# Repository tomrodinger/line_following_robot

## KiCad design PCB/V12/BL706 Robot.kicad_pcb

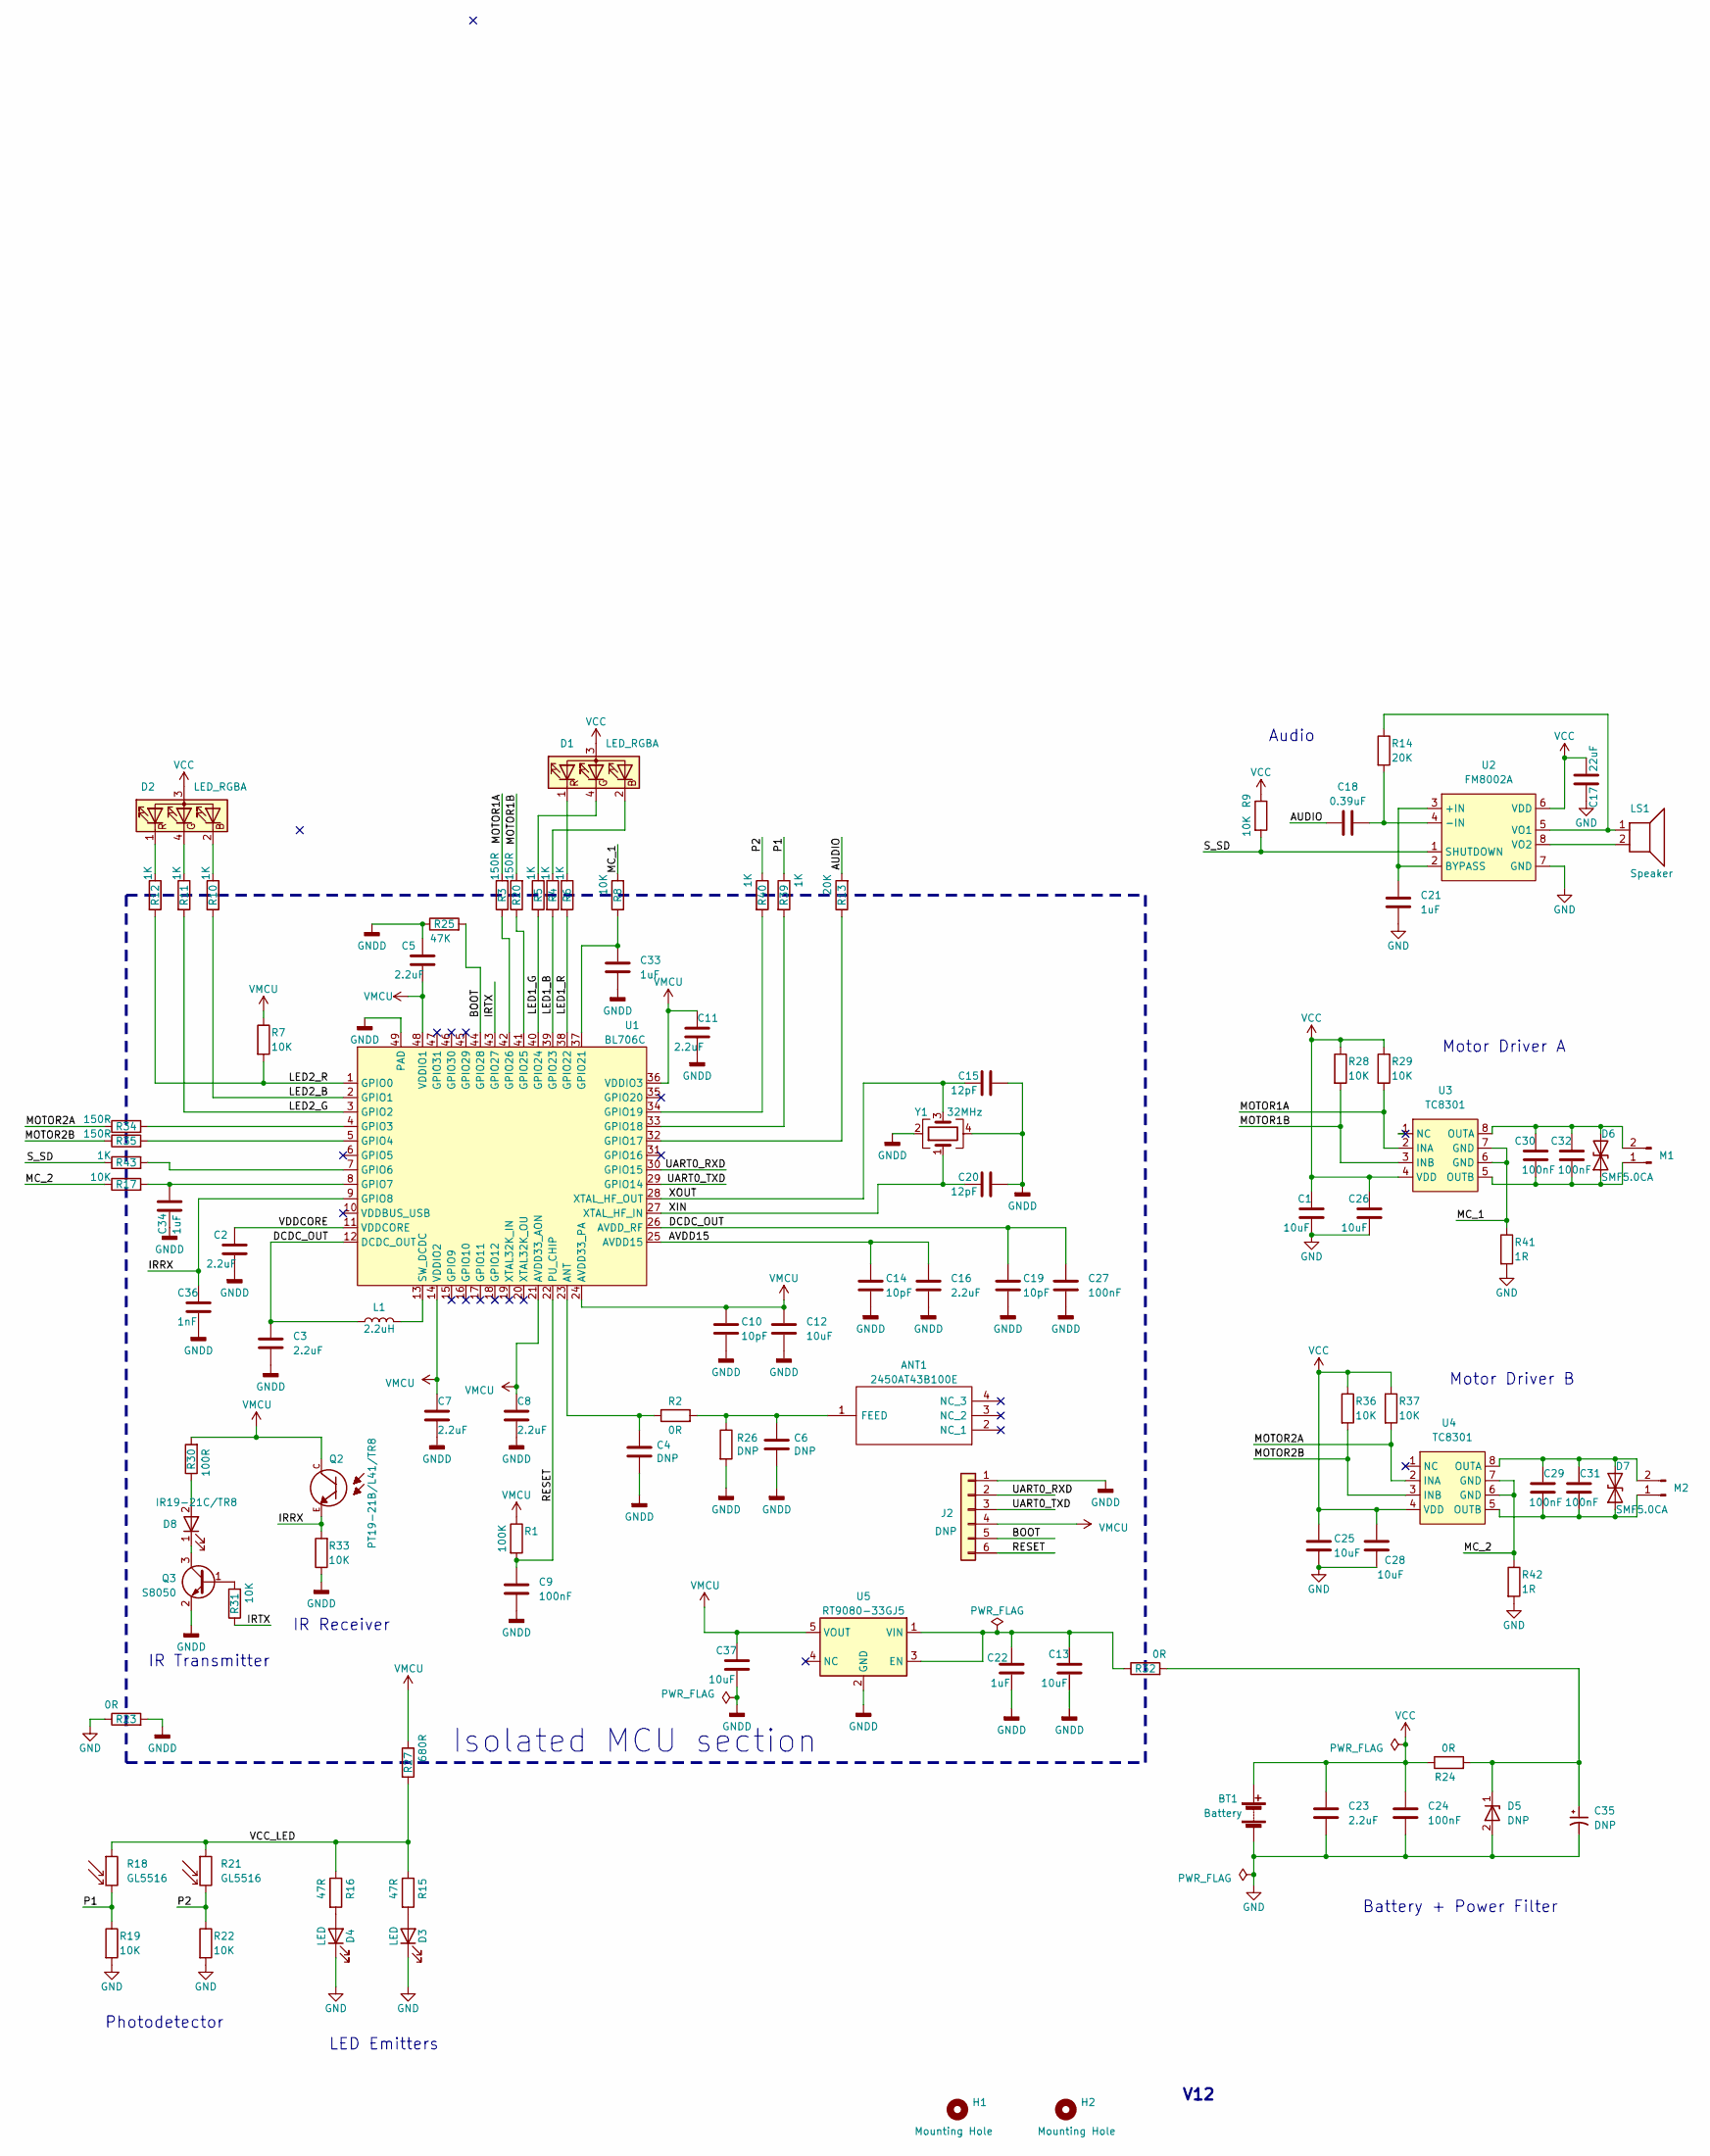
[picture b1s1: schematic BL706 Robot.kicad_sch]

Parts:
ANT1: 2450AT43B100E; LCSC C2917721
BT1: Battery; JST_PH_B2B-PH-K_1x02_P2.00mm_Vertical; LCSC C131337
C1, C12, C13, C25, C26, C28: 10uF; C_0603_1608Metric; LCSC C96446
C2, C3, C5, C7, C8, C11, C16, C23: 2.2uF; C_0402_1005Metric; LCSC C12530
C4, C6: DNP; C_0402_1005Metric
C9, C24, C27, C29, C30, C31, C32: 100nF; C_0402_1005Metric; LCSC C307331
C10, C14, C19: 10pF; C_0402_1005Metric; LCSC C32949
C15, C20: 12pF; C_0402_1005Metric; LCSC C1547
C17: 22uF; C_0603_1608Metric; LCSC C162690
C18: 0.39uF; C_0603_1608Metric; LCSC C309480
C21, C22: 1uF; C_0603_1608Metric; LCSC C15849
C33, C34: 1uF; C_0402_1005Metric; LCSC C52923
C35: DNP; CP_Elec_8x10.5; LCSC DNP
C36: 1nF; C_0402_1005Metric; LCSC C1523
C37: 10uF; C_1206_3216Metric; LCSC C13585
D1, D2: LED_RGBA; FM-B2020RGBA-HG; LCSC C108793
D3, D4: LED; LED_D3.0mm_Horizontal_O1.27mm_Z2.0mm
D5: DNP; D_MELF; LCSC DNP
D6, D7: SMF5.0CA; D_SOD-123F; LCSC C320548
D8: IR19-21C/TR8; IR19-21C-TR8; LCSC C142316
H1, H2: Mounting Hole; MountingHole_3mm
J2: DNP; PinHeader_1x06_P1.27mm_Vertical
L1: 2.2uH; L_0805_2012Metric; LCSC C86089
LS1: Speaker; JST_XH_B2B-XH-A_1x02_P2.50mm_Vertical; LCSC C158012
M1, M2: Conn_01x02_Male; JST_XH_B2B-XH-A_1x02_P2.50mm_Vertical; LCSC C158012
Q2: PT19-21B/L41/TR8; XDCR_PT19-21B_L41_TR8; LCSC C131258
Q3: S8050; SOT-23-3; LCSC C2926165
R1: 100K; R_0402_1005Metric; LCSC C25741
R2: 0R; R_0402_1005Metric; LCSC C17168
R3, R20, R34, R35: 150R; R_0402_1005Metric; LCSC C25082
R4, R5, R6, R10, R11, R12, R39, R40, R43: 1K; R_0402_1005Metric; LCSC C11702
R7, R8, R9, R17, R19, R22, R28, R29, R31, R33: 10K; R_0402_1005Metric; LCSC C25744
R13, R14: 20K; R_0402_1005Metric; LCSC C25765
R15, R16: 47R; R_0402_1005Metric; LCSC C25118
R18, R21: GL5516; R_LDR_5.0x4.1mm_P3mm_Vertical; LCSC C125626
R23, R24, R32: 0R; R_1206_3216Metric; LCSC C17888
R25: 47K; R_0402_1005Metric; LCSC C25792
R26: DNP; R_0402_1005Metric
R27: 680R; R_0805_2012Metric; LCSC C17798
R30: 100R; R_0402_1005Metric; LCSC C25076
R36, R37: 10K; R_0402_1005Metric; LCSC PN C25744
R41, R42: 1R; R_1206_3216Metric; LCSC C17928
U1: BL706C; QFN-48-1EP_6x6mm_P0.4mm_EP4.3x4.3mm; LCSC C2874060
U2: FM8002A; SOP-8_3.9x4.9mm_P1.27mm; LCSC C94625
U3, U4: TC8301; SOP-8_3.9x4.9mm_P1.27mm; LCSC C2887481
U5: RT9080-33GJ5; TSOT-23-5; LCSC C841192
Y1: 32MHz; Crystal_SMD_2016-4Pin_2.0x1.6mm; LCSC C255896

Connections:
/AUDIO: C18.1, R13.2
/AVDD15: C14.1, C16.1, U1.25 (AVDD15)
/BOOT: J2.5, R25.2, U1.44 (GPIO28)
/DCDC_OUT: C3.1, C19.1, C27.1, L1.1, U1.12 (DCDC_OUT), U1.26 (AVDD_RF)
/IRRX: C36.1, Q2.E, R33.2, U1.9 (GPIO8)
/IRTX: R31.1, U1.43 (GPIO27)
/LED1_B: R4.2, U1.39 (GPIO23)
/LED1_G: R5.2, U1.40 (GPIO24)
/LED1_R: R6.2, U1.38 (GPIO22)
/LED2_B: R10.2, U1.2 (GPIO1)
/LED2_G: R11.2, U1.3 (GPIO2)
/LED2_R: R7.2, R12.2, U1.1 (GPIO0)
/MC_1: R8.2, R41.1, U3.6 (GND), U3.7 (GND)
/MC_2: R17.1, R42.1, U4.6 (GND), U4.7 (GND)
/MOTOR1A: R3.2, R29.2, U3.2 (INA)
/MOTOR1B: R20.2, R28.2, U3.3 (INB)
/MOTOR2A: R34.1, R37.2, U4.2 (INA)
/MOTOR2B: R35.1, R36.2, U4.3 (INB)
/P1: R18.2, R19.1, R39.1
/P2: R21.2, R22.1, R40.1
/RESET: C9.1, J2.6, R1.2, U1.22 (PU_CHIP)
/S_SD: R9.2, R43.1, U2.1 (SHUTDOWN)
/UART0_RXD: J2.2, U1.30 (GPIO15)
/UART0_TXD: J2.3, U1.29 (GPIO14)
/VCC_LED: R15.1, R16.1, R18.1, R21.1, R27.2
/VDDCORE: C2.1, U1.11 (VDDCORE)
/XIN: C20.2, U1.27 (XTAL_HF_IN), Y1.1
/XOUT: C15.2, U1.28 (XTAL_HF_OUT), Y1.3
GND: BT1.2 (-), C1.2, C17.2, C21.2, C23.2, C24.2, C25.2, C26.2, C28.2, C35.2, D3.1 (K), D4.1 (K), D5.2 (A), R19.2, R22.2, R23.1, R41.2, R42.2, U2.7 (GND)
GNDD: C2.2, C3.2, C4.2, C5.1, C6.2, C7.2, C8.2, C9.2, C10.2, C11.1, C12.2, C13.2, C14.2, C15.1, C16.2, C19.2, C20.1, C22.2, C27.2, C33.2, C34.2, C36.2, C37.2, J2.1, Q3.2 (E), R23.2, R25.1, R26.2, R33.1, U1.49 (PAD), U5.2 (GND), Y1.2, Y1.4
unnamed: ANT1.1 (FEED), C6.1, R2.2, R26.1
unnamed: D1.2 (BK), R4.1
unnamed: D1.4 (GK), R5.1
unnamed: D1.1 (RK), R6.1
unnamed: D2.2 (BK), R10.1
unnamed: D2.4 (GK), R11.1
unnamed: D2.1 (RK), R12.1
unnamed: D3.2 (A), R15.2
unnamed: D4.2 (A), R16.2
unnamed: C35.1, D5.1 (K), R24.2, R32.2
unnamed: C30.2, C32.2, D6.1 (A1), M1.1, U3.5 (OUTB)
unnamed: C30.1, C32.1, D6.2 (A2), M1.2, U3.8 (OUTA)
unnamed: C29.2, C31.2, D7.1 (A1), M2.1, U4.5 (OUTB)
unnamed: C29.1, C31.1, D7.2 (A2), M2.2, U4.8 (OUTA)
unnamed: D8.2 (A), R30.1
unnamed: D8.1 (K), Q3.3 (C)
unnamed: Q3.1 (B), R31.2
unnamed: C4.1, R2.1, U1.23 (ANT)
unnamed: R34.2, U1.4 (GPIO3)
unnamed: R35.2, U1.5 (GPIO4)
unnamed: R43.2, U1.7 (GPIO6)
unnamed: C34.1, R17.2, U1.8 (GPIO7)
unnamed: R13.1, U1.32 (GPIO17)
unnamed: R39.2, U1.33 (GPIO18)
unnamed: R40.2, U1.34 (GPIO19)
unnamed: C33.1, R8.1, U1.37 (GPIO21)
unnamed: R20.1, U1.41 (GPIO25)
unnamed: R3.1, U1.42 (GPIO26)
unnamed: L1.2, U1.13 (SW_DCDC)
unnamed: C21.1, U2.2 (BYPASS), U2.3 (+IN)
unnamed: C18.2, R14.2, U2.4 (-IN)
unnamed: LS1.1, R14.1, U2.5 (VO1)
unnamed: LS1.2, U2.8 (VO2)
unnamed: C13.1, C22.1, R32.1, U5.1 (VIN), U5.3 (EN)
VCC: BT1.1 (+), C1.1, C17.1, C23.1, C24.1, C25.1, C26.1, C28.1, D1.3 (A), D2.3 (A), R9.1, R24.1, R28.1, R29.1, R36.1, R37.1, U2.6 (VDD), U3.4 (VDD), U4.4 (VDD)
VPP: C5.2, C7.1, C8.1, C10.1, C11.2, C12.1, C37.1, J2.4, Q2.C, R1.1, R7.1, R27.1, R30.2, U1.14 (VDDIO2), U1.21 (AVDD33_AON), U1.24 (AVDD33_PA), U1.36 (VDDIO3), U1.48 (VDDIO1), U5.5 (VOUT)

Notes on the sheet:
Photodetector
Audio
LED Emitters
Motor Driver A
Battery + Power Filter
Isolated MCU section
V12
IR Transmitter
Motor Driver B
IR Receiver

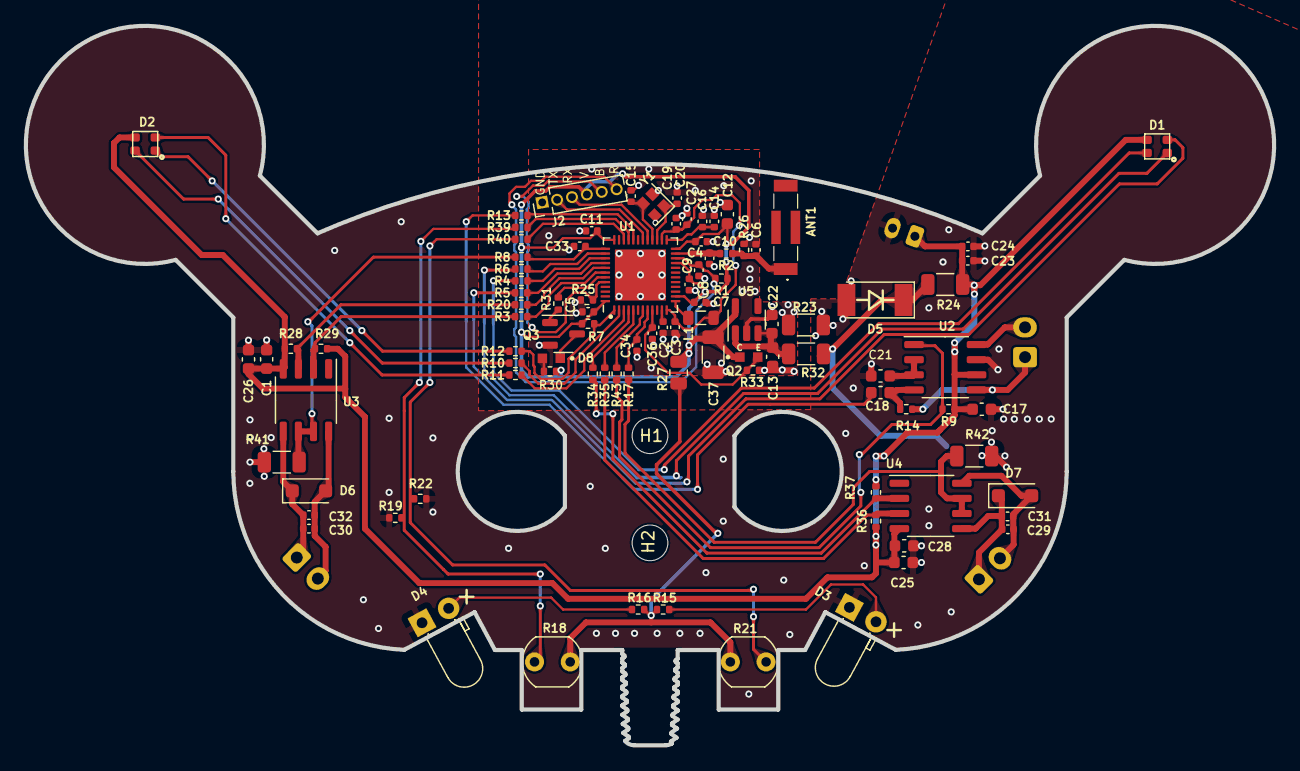
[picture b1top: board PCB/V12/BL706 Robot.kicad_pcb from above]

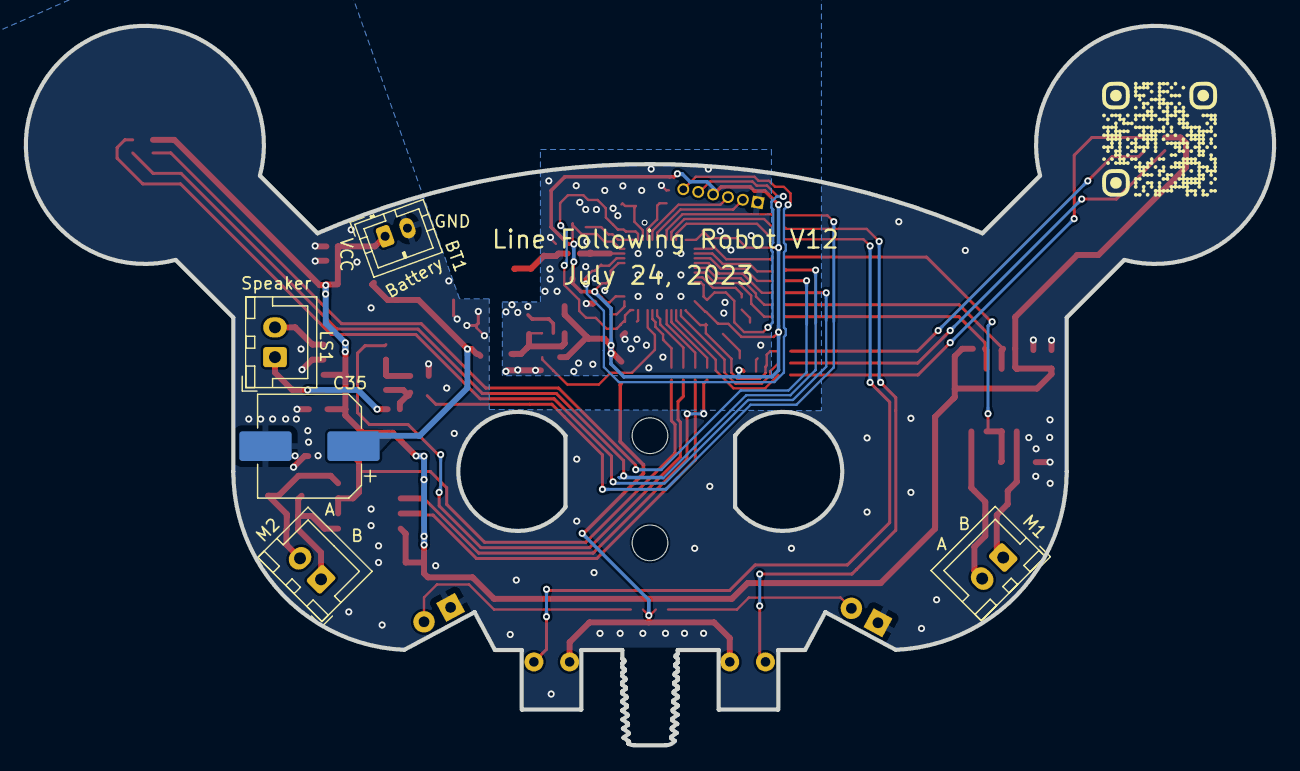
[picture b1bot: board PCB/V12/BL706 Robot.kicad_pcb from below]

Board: 2 copper layers, 104.8 x 60.4 mm, 104 parts (5 on the bottom side), 66 nets.

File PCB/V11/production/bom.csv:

Designator,Footprint,Quantity,Value,LCSC Part #
ANT1,2450AT43B100E,1,2450AT43B100E,C2917721
BT1,JST_PH_B2B-PH-K_1x02_P2.00mm_Vertical,1,Battery,C131337
"C1, C12, C25, C26, C28",603,5,10uF,C96446
"C10, C14, C19",402,3,10pF,C32949
"C11, C16, C2, C23, C3, C5, C7, C8",402,8,2.2uF,C12530
C13,CP_EIA-3528-21_Kemet-B,1,100uF,C129567
"C15, C20",402,2,12pF,C1547
C17,603,1,22uF,C162690
C18,603,1,0.39uF,C309480
C21,603,1,1uF,C105504
"C24, C27, C29, C30, C31, C32, C9",402,7,100nF,C307331
"C33, C34",402,2,1uF,C52923
C35,CP_Elec_8x10.5,1,1000uF,C99833
C36,402,1,1nF,C141053
"C4, C6, R26",402,3,DNP,
"D1, D2",FM-B2020RGBA-HG,2,LED_RGBA,C108793
D5,D_MELF,1,ZM4728A,C38989
"D6, D7",D_SOD-123F,2,SMF5.0CA,C320548
D8,IR19-21C-TR8,1,IR19-21C/TR8,C142316
"H1, H2",MountingHole_3mm,2,Mounting Hole,
J2,PinHeader_1x06_P1.27mm_Vertical,1,Conn_01x06,
L1,805,1,2.2uH,C86089
L2,805,1,100uH,C223180
LS1,JST_XH_B2B-XH-A_1x02_P2.50mm_Vertical,1,Speaker,C158012
"M1, M2",JST_XH_B2B-XH-A_1x02_P2.50mm_Vertical,2,Conn_01x02_Male,C158012
Q2,XDCR_PT19-21B_L41_TR8,1,PT19-21B/L41/TR8,C131258
Q3,SOT-23-3,1,S8050,C2926165
R1,402,1,100K,C208776
"R10, R11, R12, R39, R4, R40, R5, R6",402,8,1K,C11702
"R13, R14",402,2,20K,C25765
"R15, R16",402,2,47R,C284589
"R17, R19, R22, R28, R29, R31, R33, R36, R37, R43, R7, R8, R9",402,13,10K,C25744
R2,402,1,0R,C102745
"R20, R3, R34, R35",402,4,150R,C140202
R23,1206,1,10R,C326706
R24,1206,1,3R,C3152278
R25,402,1,47K,C163830
R27,805,1,100R,C2907218
R30,402,1,33R,C208868
"R41, R42",1206,2,1R,C17928
U1,QFN-48-1EP_6x6mm_P0.4mm_EP4.3x4.3mm,1,BL706C,C2874060
U2,SOP-8_3.9x4.9mm_P1.27mm,1,FM8002A,C94625
"U3, U4",SOP-8_3.9x4.9mm_P1.27mm,2,TC8301,C2887481
Y1,Crystal_SMD_2016-4Pin_2.0x1.6mm,1,32MHz,C255896

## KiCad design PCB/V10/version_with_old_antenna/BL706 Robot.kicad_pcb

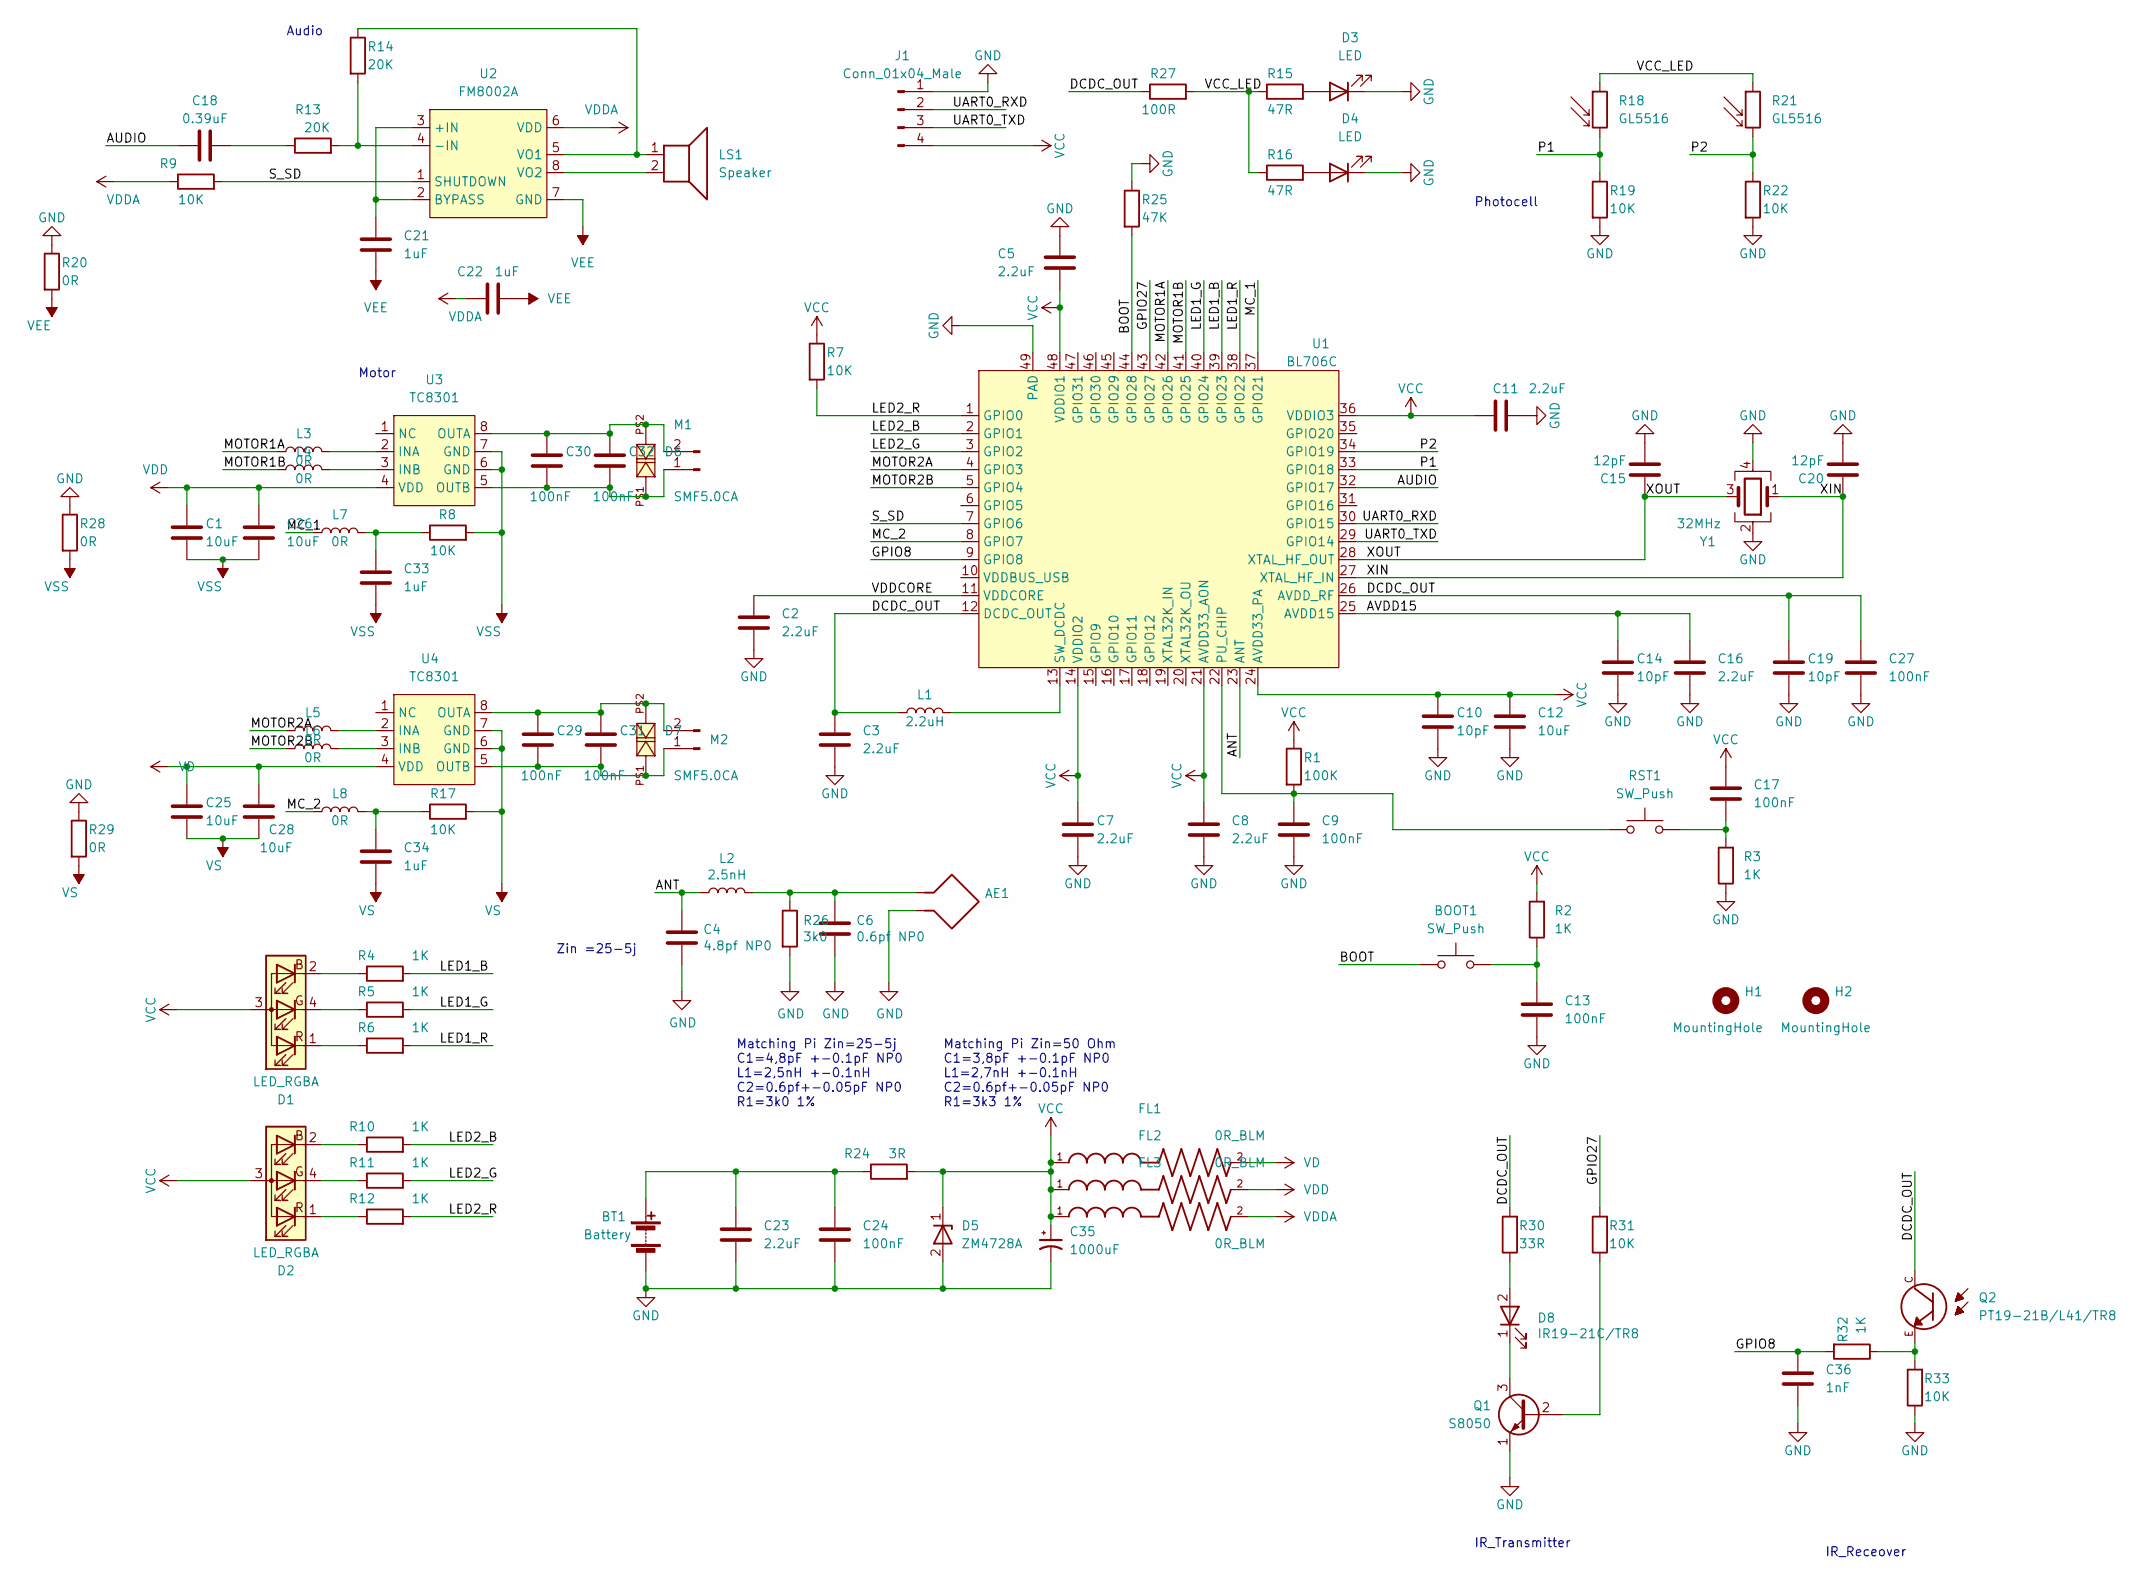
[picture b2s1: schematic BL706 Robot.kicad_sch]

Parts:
AE1: Antenna_Loop; BLE_2437_LOOP_2
BOOT1: SW_Push; SW_SPST_EVQPE1; LCSC PN C720477
BT1: Battery; JST_PH_B2B-PH-K_1x02_P2.00mm_Vertical
C1, C12, C25, C26, C28: 10uF; C_0603_1608Metric; LCSC PN C96446
C2, C3, C5, C7, C8, C11, C16, C23: 2.2uF; C_0402_1005Metric; LCSC PN C12530
C4: 4.8pf NP0; C_0402_1005Metric
C6: 0.6pf NP0; C_0402_1005Metric
C9, C13, C17, C24, C27, C29, C30, C31, C32: 100nF; C_0402_1005Metric; LCSC PN C307331
C10, C14, C19: 10pF; C_0402_1005Metric; LCSC PN C32949
C15: 12pF; C_0402_1005Metric
C18: 0.39uF; C_0603_1608Metric
C20: 12pF; C_0402_1005Metric; LCSC PN C1547
C21, C22: 1uF; C_0603_1608Metric
C33, C34: 1uF; C_0402_1005Metric; LCSC PN C52923
C35: 1000uF; CP_Elec_8x10.5; LCSC C99833
C36: 1nF; C_0402_1005Metric; LCSC PN C307331
D1, D2: LED_RGBA; FM-B2020RGBA-HG; LCSC PN C108793
D3, D4: LED; LED_D3.0mm_Horizontal_O1.27mm_Z2.0mm
D5: ZM4728A; D_MELF; LCSC C38989
D6, D7: SMF5.0CA; SOD-123FL
D8: IR19-21C/TR8; IR19-21C-TR8
FL1, FL2, FL3: 0R_BLM; L_0603_1608Metric
H1, H2: MountingHole; MountingHole_3mm
J1: Conn_01x04_Male; PinHeader_1x04_P2.54mm_Vertical
L1: 2.2uH; L_0805_2012Metric; LCSC PN C86089
L2: 2.5nH; L_0402_1005Metric
L3, L4, L5, L6, L7, L8: 0R; L_0603_1608Metric; LCSC PN C86089
LS1: Speaker; JST_XH_B2B-XH-A_1x02_P2.50mm_Vertical; LCSC C158012
M1, M2: Conn_01x02_Male; JST_XH_B2B-XH-A_1x02_P2.50mm_Vertical; LCSC C158012
Q1: S8050; SOT-23-3
Q2: PT19-21B/L41/TR8; XDCR_PT19-21B_L41_TR8; PARTREV 6
R1: 100K; R_0402_1005Metric; LCSC PN C25744
R2, R3, R4, R5, R6, R10, R11, R12, R32: 1K; R_0402_1005Metric; LCSC PN C11702
R7, R8, R9, R17, R19, R22: 10K; R_0402_1005Metric; LCSC PN C25744
R13, R14: 20K; R_0402_1005Metric; LCSC PN C25765
R15, R16: 47R; R_0402_1005Metric
R18, R21: GL5516; R_LDR_5.0x4.1mm_P3mm_Vertical
R20, R28, R29: 0R; R_1206_3216Metric; LCSC PN C17928
R24: 3R; R_1206_3216Metric
R25: 47K; R_0402_1005Metric
R26: 3k0; R_0402_1005Metric
R27: 100R; R_0805_2012Metric
R30: 33R; R_0402_1005Metric; LCSC PN C11702
R31, R33: 10K; R_0402_1005Metric; LCSC PN C11702
RST1: SW_Push; SW_SPST_EVQPE1; LCSC PN C720477
U1: BL706C; QFN-48-1EP_6x6mm_P0.4mm_EP4.3x4.3mm
U2: FM8002A; SOP-8_3.9x4.9mm_P1.27mm; LCSC C94625
U3, U4: TC8301; SOP-8_3.9x4.9mm_P1.27mm
Y1: 32MHz; Crystal_SMD_2016-4Pin_2.0x1.6mm; LCSC PN C255896

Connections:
/ANT: C4.1, L2.1, U1.23 (ANT)
/AUDIO: C18.1, U1.32 (GPIO17)
/AVDD15: C14.1, C16.1, U1.25 (AVDD15)
/BOOT: BOOT1.1, R25.2, U1.44 (GPIO28)
/DCDC_OUT: C3.1, C19.1, C27.1, L1.1, Q2.C, R27.1, R30.2, U1.12 (DCDC_OUT), U1.26 (AVDD_RF)
/GPIO8: C36.1, R32.2, U1.9 (GPIO8)
/GPIO27: R31.2, U1.43 (GPIO27)
/LED1_B: R4.2, U1.39 (GPIO23)
/LED1_G: R5.2, U1.40 (GPIO24)
/LED1_R: R6.2, U1.38 (GPIO22)
/LED2_B: R10.2, U1.2 (GPIO1)
/LED2_G: R11.2, U1.3 (GPIO2)
/LED2_R: R7.2, R12.2, U1.1 (GPIO0)
/MC_1: L7.1, U1.37 (GPIO21)
/MC_2: L8.1, U1.8 (GPIO7)
/MOTOR1A: L3.1, U1.42 (GPIO26)
/MOTOR1B: L4.1, U1.41 (GPIO25)
/MOTOR2A: L5.1, U1.4 (GPIO3)
/MOTOR2B: L6.1, U1.5 (GPIO4)
/P1: R18.2, R19.1, U1.33 (GPIO18)
/P2: R21.2, R22.1, U1.34 (GPIO19)
/S_SD: R9.2, U1.7 (GPIO6), U2.1 (SHUTDOWN)
/UART0_RXD: J1.2, U1.30 (GPIO15)
/UART0_TXD: J1.3, U1.29 (GPIO14)
/VCC_LED: R15.1, R16.1, R18.1, R21.1, R27.2
/VDDCORE: C2.1, U1.11 (VDDCORE)
/XIN: C20.1, U1.27 (XTAL_HF_IN), Y1.1
/XOUT: C15.1, U1.28 (XTAL_HF_OUT), Y1.3
GND: AE1.2, BT1.2 (-), C2.2, C3.2, C4.2, C5.1, C6.2, C7.2, C8.2, C9.2, C10.2, C11.1, C12.2, C13.2, C14.2, C15.2, C16.2, C19.2, C20.2, C23.2, C24.2, C27.2, C35.2, C36.2, D3.1 (K), D4.1 (K), D5.2 (A), J1.1, Q1.1 (E), R3.1, R19.2, R20.1, R22.2, R25.1, R26.2, R28.1, R29.1, R33.1, U1.49 (PAD), Y1.2, Y1.4
unnamed: AE1.1, C6.1, L2.2, R26.1
unnamed: BOOT1.2, C13.1, R2.1
unnamed: C9.1, R1.2, RST1.1, U1.22 (PU_CHIP)
unnamed: C17.2, R3.2, RST1.2
unnamed: C18.2, R13.1
unnamed: C21.1, U2.2 (BYPASS), U2.3 (+IN)
unnamed: BT1.1 (+), C23.1, C24.1, R24.1
unnamed: C29.1, C31.1, D7.P$2, M2.2, U4.8 (OUTA)
unnamed: C29.2, C31.2, D7.P$1, M2.1, U4.5 (OUTB)
unnamed: C30.1, C32.1, D6.P$2, M1.2, U3.8 (OUTA)
unnamed: C30.2, C32.2, D6.P$1, M1.1, U3.5 (OUTB)
unnamed: C33.1, L7.2, R8.1
unnamed: C34.1, L8.2, R17.1
unnamed: D1.1 (RK), R6.1
unnamed: D1.2 (BK), R4.1
unnamed: D1.4 (GK), R5.1
unnamed: D2.1 (RK), R12.1
unnamed: D2.2 (BK), R10.1
unnamed: D2.4 (GK), R11.1
unnamed: D3.2 (A), R15.2
unnamed: D4.2 (A), R16.2
unnamed: D8.1 (K), Q1.3 (C)
unnamed: D8.2 (A), R30.1
unnamed: L1.2, U1.13 (SW_DCDC)
unnamed: LS1.1, R14.1, U2.5 (VO1)
unnamed: LS1.2, U2.8 (VO2)
unnamed: Q1.2 (B), R31.1
unnamed: Q2.E, R32.1, R33.2
unnamed: R13.2, R14.2, U2.4 (-IN)
unnamed: L3.2, U3.2 (INA)
unnamed: L4.2, U3.3 (INB)
unnamed: L5.2, U4.2 (INA)
unnamed: L6.2, U4.3 (INB)
VCC: C5.2, C7.1, C8.1, C10.1, C11.2, C12.1, C17.1, C35.1, D1.3 (A), D2.3 (A), D5.1 (K), FL1.1, FL2.1, FL3.1, J1.4, R1.1, R2.2, R7.1, R24.2, U1.14 (VDDIO2), U1.21 (AVDD33_AON), U1.24 (AVDD33_PA), U1.36 (VDDIO3), U1.48 (VDDIO1)
VD: C25.1, C28.1, FL1.2, U4.4 (VDD)
VDD: C1.1, C26.1, FL2.2, U3.4 (VDD)
VDDA: C22.1, FL3.2, R9.1, U2.6 (VDD)
VEE: C21.2, C22.2, R20.2, U2.7 (GND)
VS: C25.2, C28.2, C34.2, R17.2, R29.2, U4.6 (GND), U4.7 (GND)
VSS: C1.2, C26.2, C33.2, R8.2, R28.2, U3.6 (GND), U3.7 (GND)

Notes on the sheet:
Photocell
Zin =25-5j
Matching Pi Zin=25-5j C1=4,8pF +-0.1pF NP0 L1=2,5nH +-0.1nH C2=0.6pf+-0.05pF NP0 R1=3k0 1%
Audio
Motor
IR_Transmitter
Matching Pi Zin=50 Ohm C1=3,8pF +-0.1pF NP0 L1=2,7nH +-0.1nH C2=0.6pf+-0.05pF NP0 R1=3k3 1%
IR_Receover

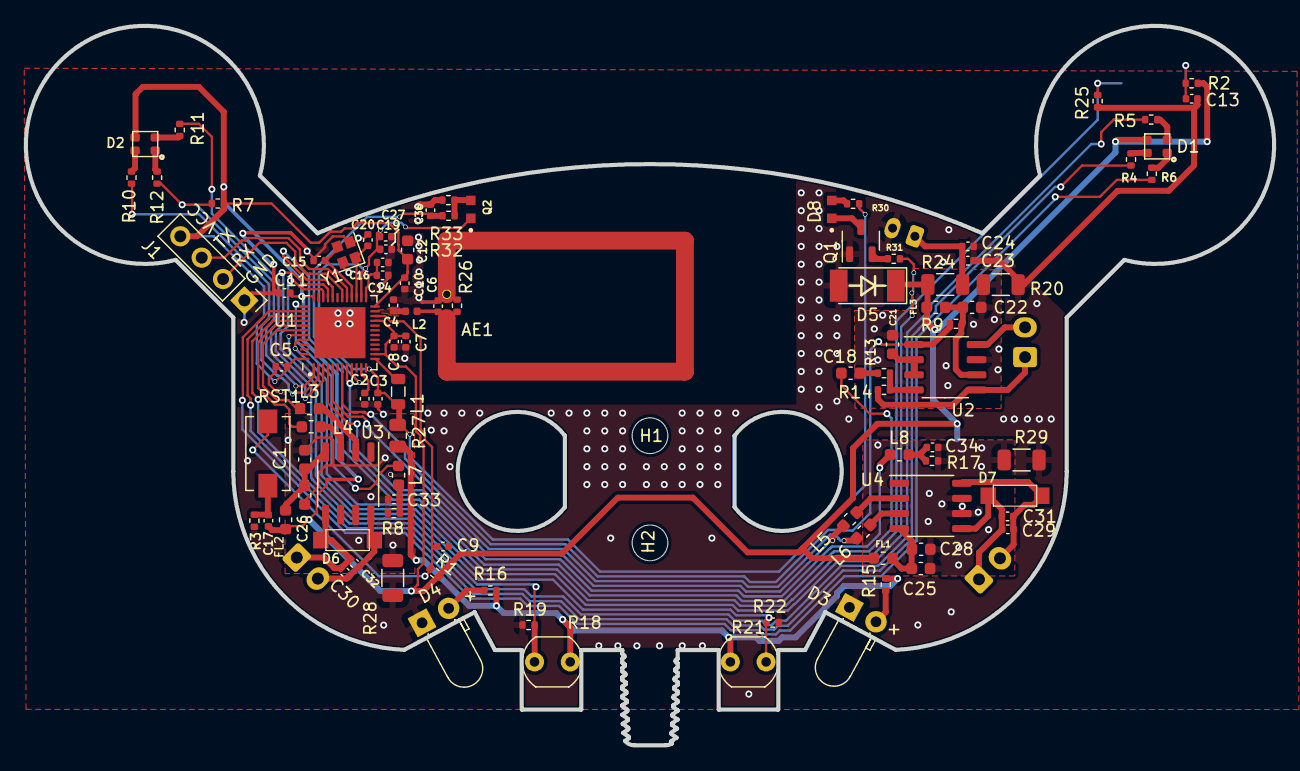
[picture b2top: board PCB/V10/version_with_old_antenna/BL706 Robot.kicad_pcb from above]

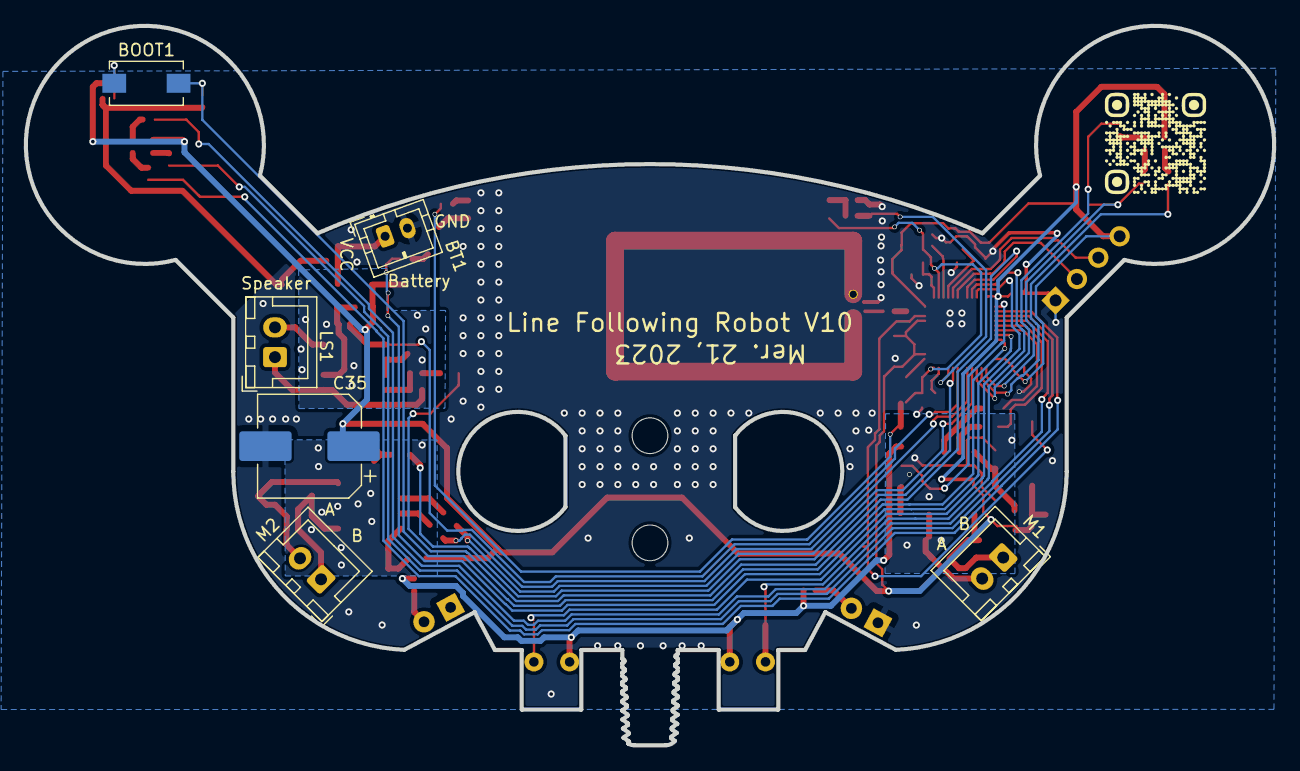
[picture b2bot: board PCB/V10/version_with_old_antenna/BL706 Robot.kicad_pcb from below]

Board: 2 copper layers, 104.8 x 60.4 mm, 104 parts (6 on the bottom side), 69 nets.
